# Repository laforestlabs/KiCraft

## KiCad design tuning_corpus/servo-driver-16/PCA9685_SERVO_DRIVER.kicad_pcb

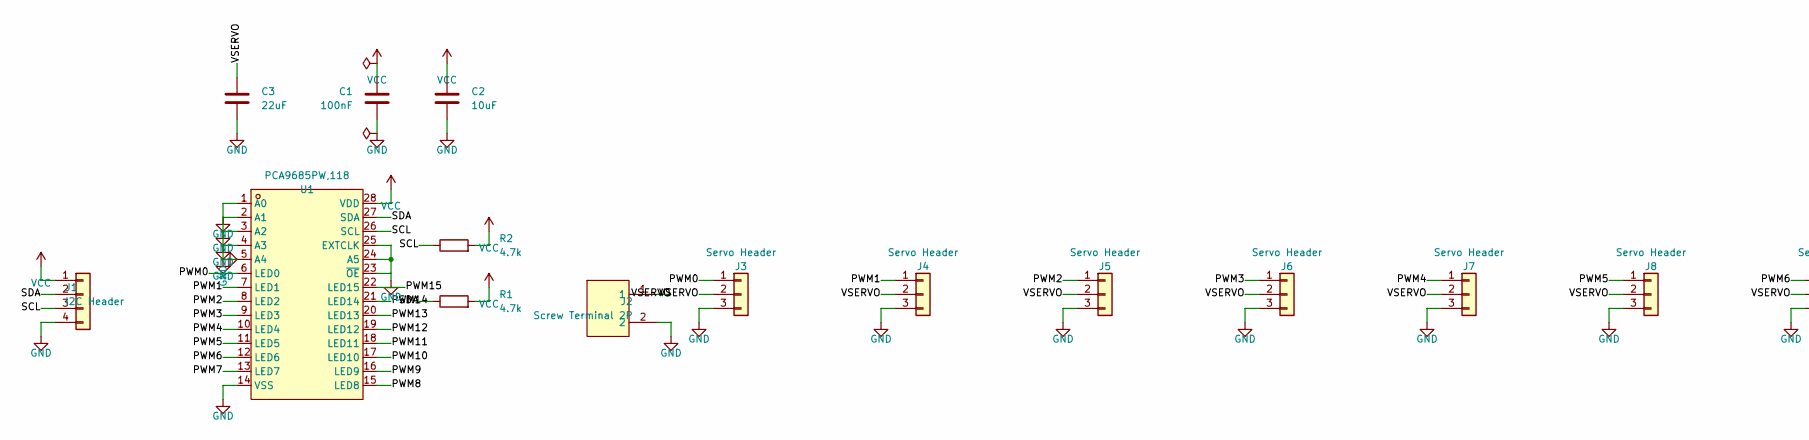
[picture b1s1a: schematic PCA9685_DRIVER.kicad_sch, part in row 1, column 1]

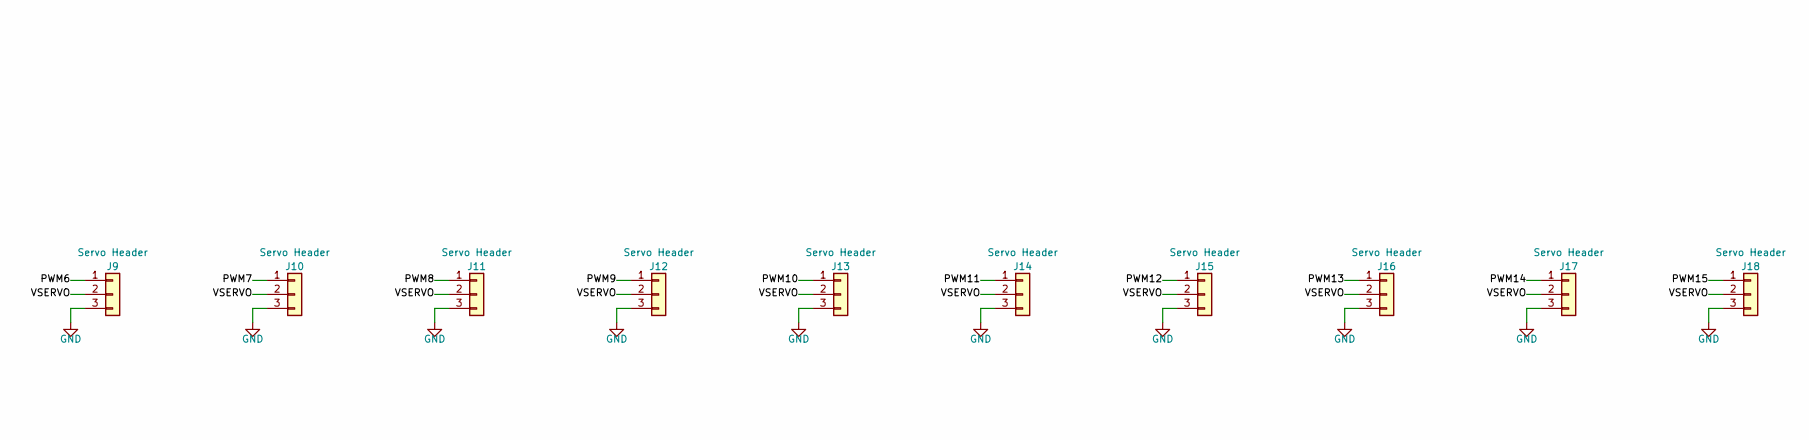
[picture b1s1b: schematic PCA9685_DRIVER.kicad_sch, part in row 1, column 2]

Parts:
C1: 100nF; C_0805_2012Metric
C2: 10uF; C_0805_2012Metric
C3: 22uF; C_1206_3216Metric
J1: I2C Header; PinHeader_1x04_P2.54mm_Vertical
J2: Screw Terminal 2P; CONN-TH_WJ126V-5.0-2P
J3, J4, J5, J6, J7, J8, J9, J10, J11, J12, J13, J14, J15, J16, J17, J18: Servo Header; PinHeader_1x03_P2.54mm_Vertical
R1, R2: 4.7k; R_0805_2012Metric
U1: PCA9685PW,118; TSSOP-28_L9.7-W4.4-P0.65-LS6.4-TL

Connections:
PWM0: J3.1, U1.6 (LED0)
PWM1: J4.1, U1.7 (LED1)
PWM2: J5.1, U1.8 (LED2)
PWM3: J6.1, U1.9 (LED3)
PWM4: J7.1, U1.10 (LED4)
PWM5: J8.1, U1.11 (LED5)
PWM6: J9.1, U1.12 (LED6)
PWM7: J10.1, U1.13 (LED7)
PWM8: J11.1, U1.15 (LED8)
PWM9: J12.1, U1.16 (LED9)
PWM10: J13.1, U1.17 (LED10)
PWM11: J14.1, U1.18 (LED11)
PWM12: J15.1, U1.19 (LED12)
PWM13: J16.1, U1.20 (LED13)
PWM14: J17.1, U1.21 (LED14)
PWM15: J18.1, U1.22 (LED15)
SCL: J1.3, R2.1, U1.26 (SCL)
SDA: J1.2, R1.1, U1.27 (SDA)
VSERVO: C3.1, J2.1, J3.2, J4.2, J5.2, J6.2, J7.2, J8.2, J9.2, J10.2, J11.2, J12.2, J13.2, J14.2, J15.2, J16.2, J17.2, J18.2

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
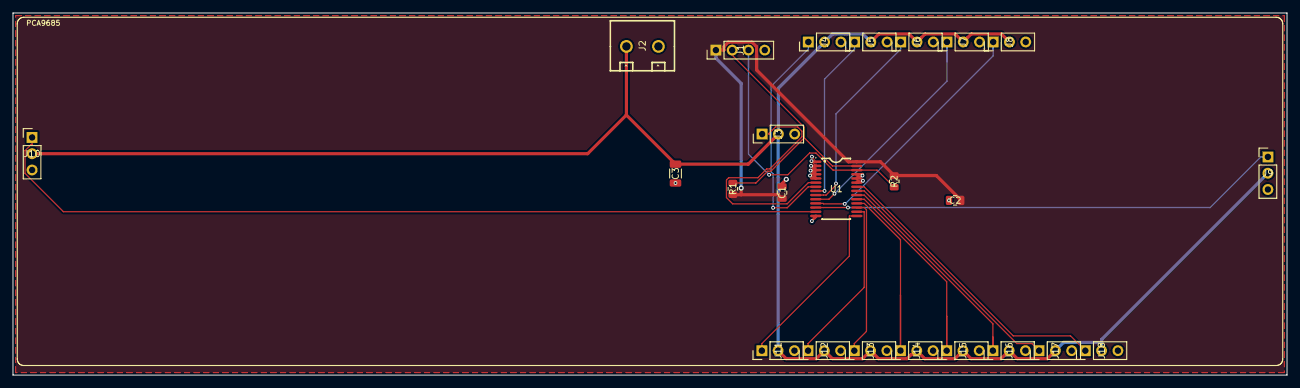
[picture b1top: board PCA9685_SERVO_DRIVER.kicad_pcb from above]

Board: 2 copper layers, 198.8 x 56.5 mm, 24 parts (0 on the bottom side), 21 nets.

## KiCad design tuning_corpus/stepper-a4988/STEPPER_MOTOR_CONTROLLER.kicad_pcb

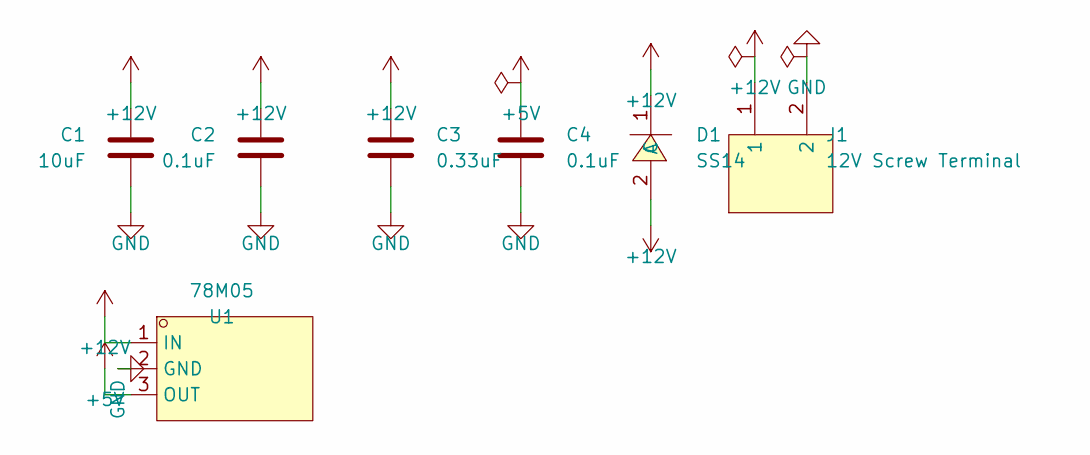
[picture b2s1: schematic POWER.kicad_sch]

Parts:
C1: 10uF; C_0805_2012Metric
C2, C4: 0.1uF; C_0805_2012Metric
C3: 0.33uF; C_0805_2012Metric
D1: SS14; SMA_L4.3-W2.6-LS5.0-RD
J1: 12V Screw Terminal; CONN-TH_WJ126V-5.0-2P
U1: 78M05; TO-252-2_L6.6-W6.1-P4.57-LS9.9-BR-CW

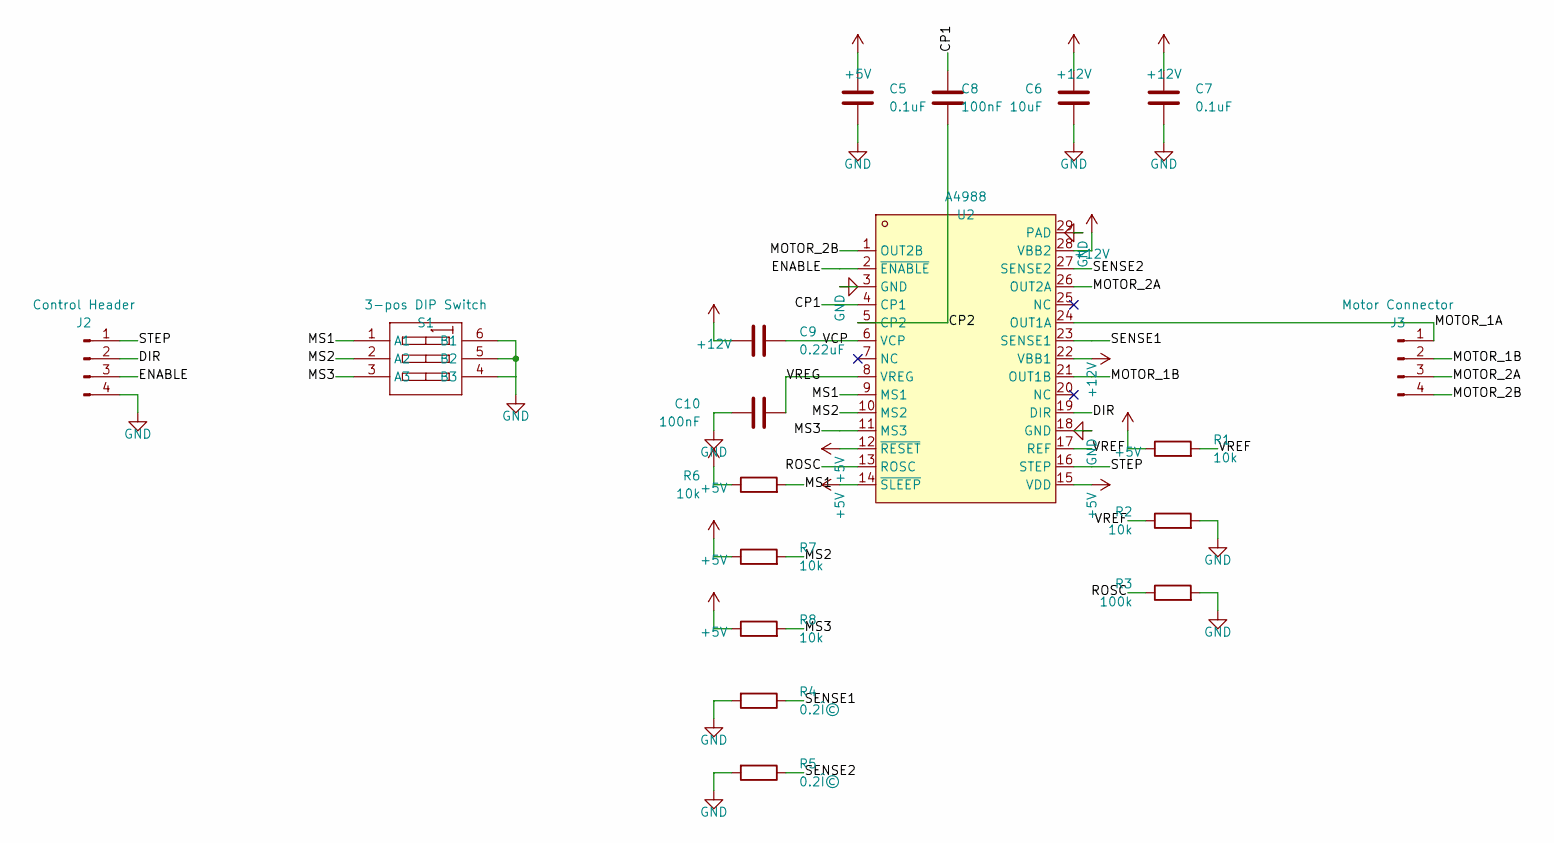
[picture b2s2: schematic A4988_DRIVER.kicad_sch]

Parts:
C5, C7: 0.1uF; C_0805_2012Metric
C6: 10uF; C_0805_2012Metric
C8, C10: 100nF; C_0805_2012Metric
C9: 0.22uF; C_0805_2012Metric
J2: Control Header; PinHeader_1x04_P2.54mm_Vertical
J3: Motor Connector; PinHeader_1x04_P2.54mm_Vertical
R1, R2, R6, R7, R8: 10k; R_0805_2012Metric
R3: 100k; R_0805_2012Metric
R4, R5: 0.2Î©; R_0805_2012Metric
S1: 3-pos DIP Switch; SW-SMD_6P-L5.4-W5.4-P1.27-LS8.4
U2: A4988; WQFN-28_L5.0-W5.0-P0.50-BL-EP3.2

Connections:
CP1: C8.1, U2.4 (CP1)
CP2: C8.2, U2.5 (CP2)
DIR: J2.2, U2.19 (DIR)
ENABLE: J2.3, U2.2 (~ENABLE)
MOTOR_1A: J3.1, U2.24 (OUT1A)
MOTOR_1B: J3.2, U2.21 (OUT1B)
MOTOR_2A: J3.3, U2.26 (OUT2A)
MOTOR_2B: J3.4, U2.1 (OUT2B)
MS1: R6.2, S1.1 (A1), U2.9 (MS1)
MS2: R7.2, S1.2 (A2), U2.10 (MS2)
MS3: R8.2, S1.3 (A3), U2.11 (MS3)
ROSC: R3.1, U2.13 (ROSC)
SENSE1: R4.1, U2.23 (SENSE1)
SENSE2: R5.1, U2.27 (SENSE2)
STEP: J2.1, U2.16 (STEP)
VCP: C9.1, U2.6 (VCP)
VREF: R1.2, R2.1, U2.17 (REF)
VREG: C10.1, U2.8 (VREG)

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
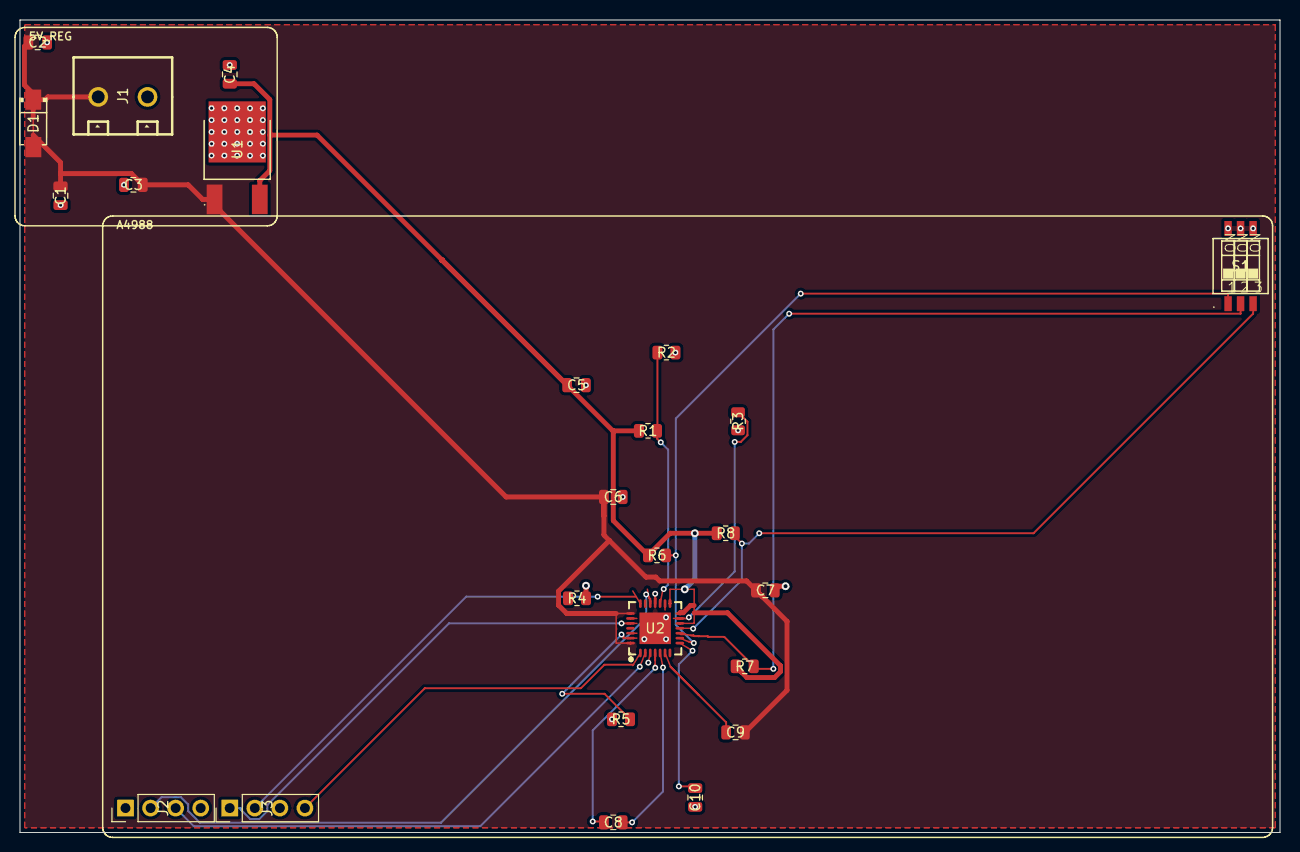
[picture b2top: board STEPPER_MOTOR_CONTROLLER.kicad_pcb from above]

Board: 2 copper layers, 127.7 x 82.3 mm, 25 parts (0 on the bottom side), 21 nets.

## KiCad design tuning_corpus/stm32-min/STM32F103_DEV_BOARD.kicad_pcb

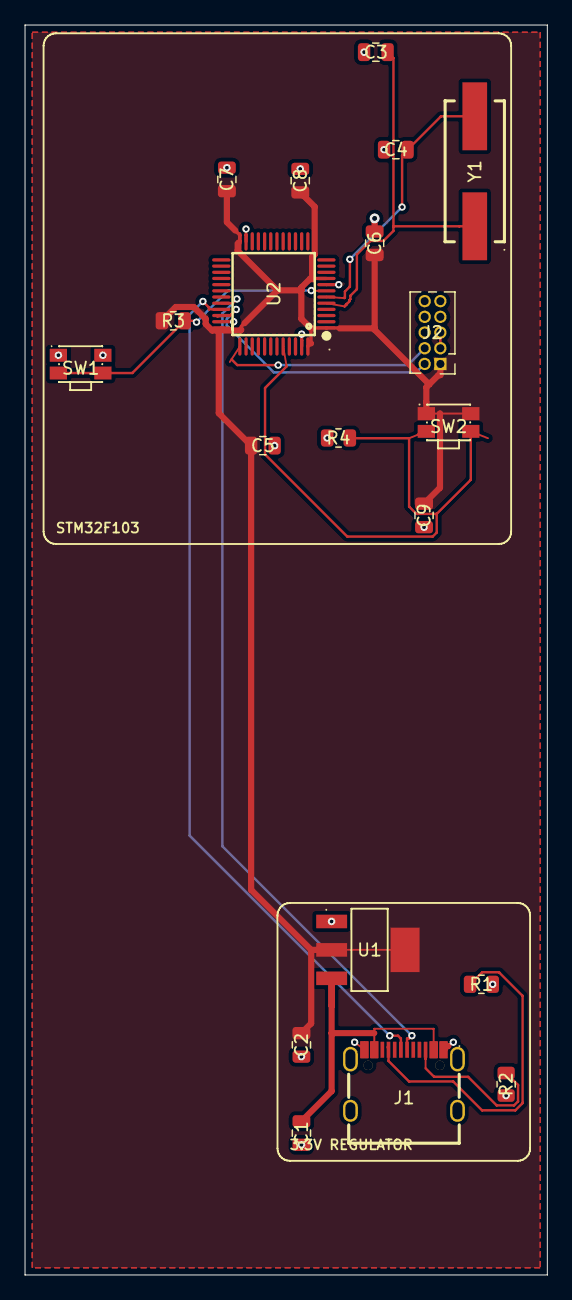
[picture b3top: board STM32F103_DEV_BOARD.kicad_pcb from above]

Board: 2 copper layers, 42.3 x 101.1 mm, 20 parts (0 on the bottom side), 13 nets.

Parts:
C1, C2, C9: 10ÂµF; C_0805_2012Metric
C3, C4: 22pF; C_0805_2012Metric
C5, C6, C7, C8: 100nF; C_0805_2012Metric
J1: TYPE-C-31-M-12; USB-C_SMD-TYPE-C-31-M-12_1
J2: SWD_2x05; PinHeader_2x05_P1.27mm_Vertical
R1, R2: 5.1k; R_0805_2012Metric
R3, R4: 10k; R_0805_2012Metric
SW1, SW2: EVQP7A01P; SW-SMD_EVQP7A01P
U1: AMS1117-3.3; SOT-223-3_L6.5-W3.4-P2.30-LS7.0-BR
U2: STM32F103C8T6; LQFP-48_L7.0-W7.0-P0.50-LS9.0-BL
Y1: 8MHz; CRYSTAL-SMD_L11.5-W4.8-LS12.7

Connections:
+3V3: C2.1, C5.1, C6.1, C7.1, C8.1, C9.1, J2.1, R3.1, SW2.1, SW2.1', U1.2, U1.4, U2.1, U2.9, U2.24, U2.36, U2.48
BOOT0: R4.1, SW2.2, SW2.2', U2.44
CC1: J1.A5, R1.1
CC2: J1.B5, R2.1
GND: C1.2, C2.2, C3.2, C4.2, C5.2, C6.2, C7.2, C8.2, C9.2, J1.1, J1.2, J1.3, J1.4, J1.A1B12, J1.B1A12, J2.3, J2.5, J2.9, R1.2, R2.2, R4.2, SW1.1, SW1.1', U1.1, U2.8, U2.23, U2.35, U2.47
NRST: R3.2, SW1.2, SW1.2', U2.7
OSC_IN: C3.1, U2.5, Y1.1
OSC_OUT: C4.1, U2.6, Y1.2
SWCLK: J2.4, U2.37
SWDIO: J2.2, U2.34
USB_DN: J1.A7, U2.32
USB_DP: J1.A6, U2.33
VBUS: C1.1, J1.A4B9, J1.B4A9, U1.3

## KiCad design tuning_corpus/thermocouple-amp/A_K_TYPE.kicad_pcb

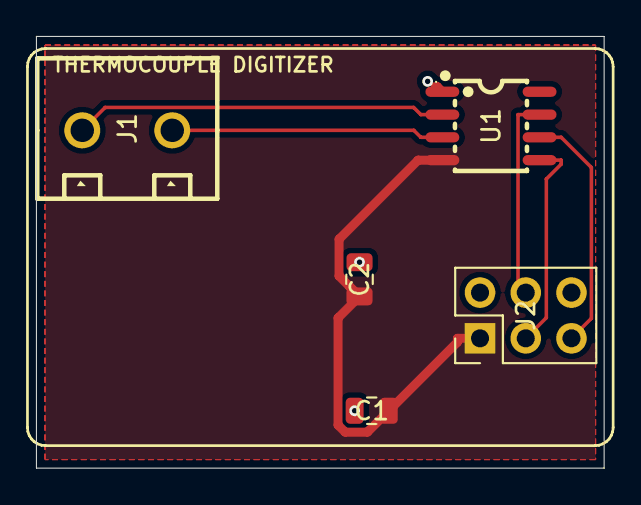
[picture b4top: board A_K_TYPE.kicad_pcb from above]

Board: 2 copper layers, 31.5 x 24.0 mm, 5 parts (0 on the bottom side), 7 nets.

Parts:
C1: 0.1uF; C_0805_2012Metric
C2: 10uF; C_0805_2012Metric
J1: 2-pin 5.08mm screw terminal; CONN-TH_WJ126V-5.0-2P
J2: 2x3 Pin Header 2.54mm; PinHeader_2x03_P2.54mm_Vertical
U1: MAX31855KASA+T; SO-8_L4.9-W3.9-P1.27-LS5.9-BL

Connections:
+3V3: C1.1, C2.1, J2.1, U1.4
CS: J2.5, U1.6
GND: C1.2, C2.2, J2.2, U1.1
SCK: J2.3, U1.5
SO: J2.4, U1.7
TC_NEG: J1.1, U1.2
TC_POS: J1.2, U1.3

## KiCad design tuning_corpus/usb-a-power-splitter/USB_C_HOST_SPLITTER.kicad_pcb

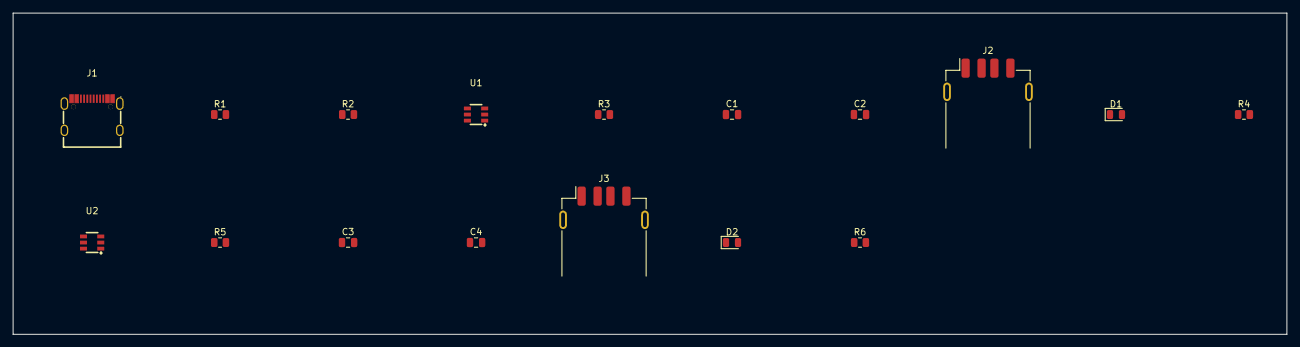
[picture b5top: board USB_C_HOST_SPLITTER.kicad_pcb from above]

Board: 2 copper layers, 199.0 x 50.2 mm, 17 parts (0 on the bottom side), 10 nets, no tracks yet.

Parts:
C1, C2, C3, C4: 1ÂµF; C_0805_2012Metric
D1, D2: Red LED; LED_0805_2012Metric
J1: TYPE-C-31-M-12; USB-C_SMD-TYPE-C-31-M-12_1
J2, J3: USB-A Receptacle; USB_A_Receptacle_GCT_USB1046
R1, R2: 5.1k; R_0805_2012Metric
R3, R5: 62k; R_0805_2012Metric
R4, R6: 330; R_0805_2012Metric
U1, U2: TPS2553DBVR; SOT-23-6_L2.9-W1.6-P0.95-LS2.8-BR

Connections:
+5V: C1.1, C3.1, J1.A4B9, J1.B4A9, U1.1, U1.3, U2.1, U2.3
CC1: J1.A5, R1.1
CC2: J1.B5, R2.1
GND: C1.2, C2.2, C3.2, C4.2, D1.1, D2.1, J1.1, J1.2, J1.3, J1.4, J1.A1B12, J1.B1A12, J2.4, J2.5, J3.4, J3.5, R1.2, R2.2, R3.2, R5.2, U1.2, U2.2
ILIM1: R3.1, U1.5
ILIM2: R5.1, U2.5
LED1_A: D1.2, R4.2
LED2_A: D2.2, R6.2
PORT1_VBUS: C2.1, J2.1, R4.1, U1.6
PORT2_VBUS: C4.1, J3.1, R6.1, U2.6

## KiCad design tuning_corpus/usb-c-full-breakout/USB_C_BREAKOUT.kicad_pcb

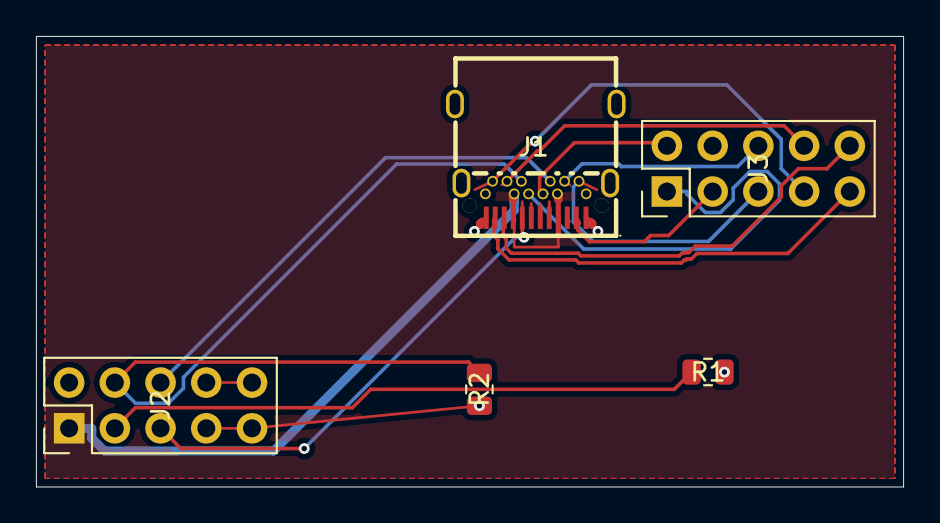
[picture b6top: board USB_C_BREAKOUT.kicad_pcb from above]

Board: 2 copper layers, 48.2 x 25.0 mm, 5 parts (0 on the bottom side), 16 nets.

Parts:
J1: USB-C 24P Receptacle; TYPE-C-SMD_TYPE-C-24P-QCHT
J2, J3: 2x5 Pin Header 2.54mm; PinHeader_2x05_P2.54mm_Vertical
R1, R2: 5.1k; R_0805_2012Metric

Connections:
CC1: J1.A5, J2.3, R1.1
CC2: J1.B5, J2.4, R2.1
D+: J1.A6, J1.B6, J3.1
D-: J1.A7, J1.B7, J3.2
GND: J1.25, J1.A1, J1.A12, J1.B1, J1.B12, J2.2, J2.7, J2.8, J2.9, J2.10, R1.2, R2.2
RX1+: J1.B11, J3.5
RX1-: J1.B10, J3.6
RX2+: J1.A11, J3.9
RX2-: J1.A10, J3.10
SBU1: J1.A8, J2.5
SBU2: J1.B8, J2.6
TX1+: J1.A2, J3.3
TX1-: J1.A3, J3.4
TX2+: J1.B2, J3.7
TX2-: J1.B3, J3.8
VBUS: J1.A4, J1.A9, J1.B4, J1.B9, J2.1
